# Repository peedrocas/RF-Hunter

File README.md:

# RF-Hunter

Tool that measures the Radio Frequency in a specific location.

My version of the RF-Hunter is a simple, small gadget made from a HMC849A chip and a GRF1201 chip. It also has two antennas, one 2.4GHz and one 5GHz. They switch periodically to measure the amount of radio frequency coming from a specific location.
This way, you can have fun while searching for what device could be emmitting those particular radio waves.

The PCB works on a common ESP32-WROOM-32 DevkitC. You can choose your own screen to use, the 3d printing models and code will need to be adapted! I decided to use a DFR0664 for myself.

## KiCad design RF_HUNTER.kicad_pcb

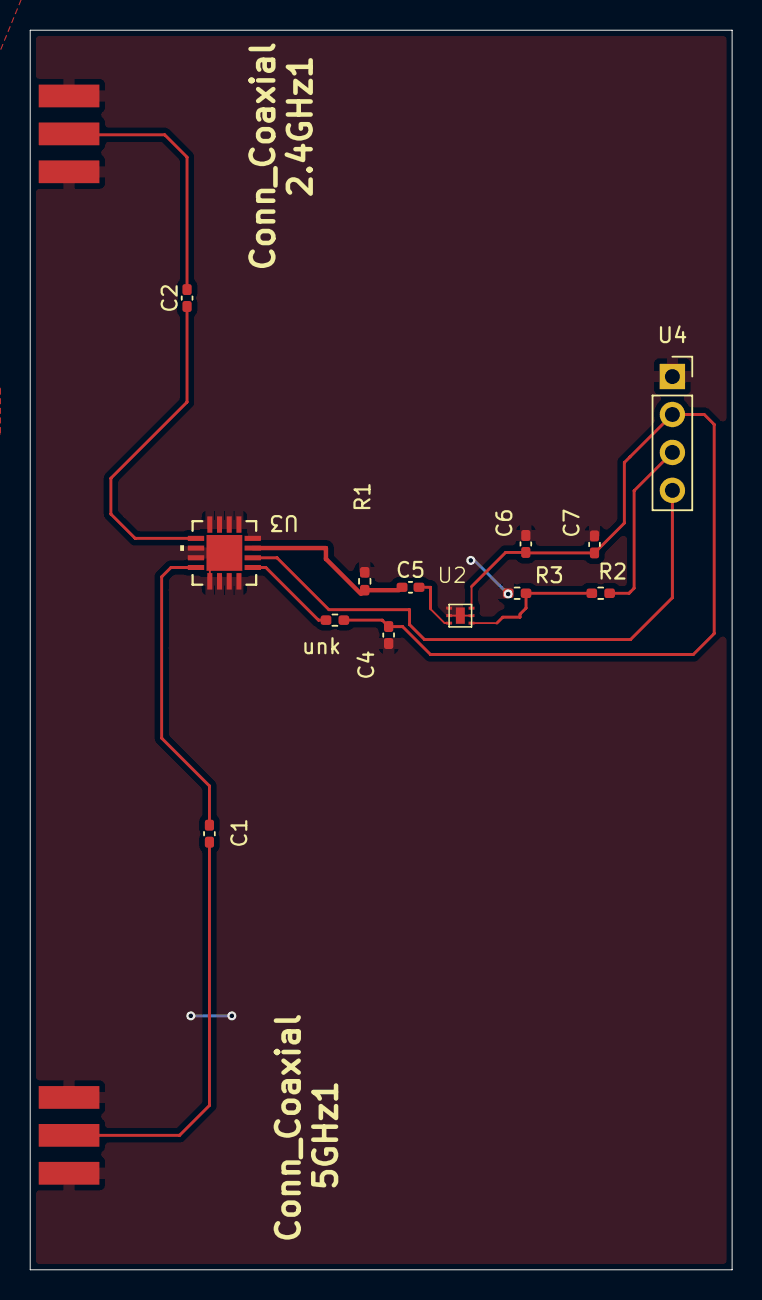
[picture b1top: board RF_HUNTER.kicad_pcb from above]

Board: 4 copper layers, 47.0 x 83.0 mm, 15 parts (0 on the bottom side), 12 nets.

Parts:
2.4GHz1, 5GHz1: Conn_Coaxial; CON-SMA-EDGE
C1, C2, C4, C7: 100pF; C_0402_1005Metric_Pad0.74x0.62mm_HandSolder
C5: 2pF; C_0402_1005Metric_Pad0.74x0.62mm_HandSolder
C6: 100nF; C_0402_1005Metric_Pad0.74x0.62mm_HandSolder
R1: 68Ω; R_0402_1005Metric_Pad0.72x0.64mm_HandSolder
R2: 10kΩ; R_0402_1005Metric_Pad0.72x0.64mm_HandSolder
R3: 20kΩ; R_0402_1005Metric_Pad0.72x0.64mm_HandSolder
U2: GRF1201
U3: HMC849A; CP_16_40_ADI-M
U4: ESP32-DevKitC; PinSocket_1x04_P2.54mm_Vertical
unk: ?; R_0402_1005Metric_Pad0.72x0.64mm_HandSolder

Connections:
GND: 2.4GHz1.2 (Ext), 2.4GHz1.3, 2.4GHz1.4, 2.4GHz1.5, 5GHz1.2 (Ext), 5GHz1.3, 5GHz1.4, 5GHz1.5, C4.1, C6.2, C7.2, R1.1, R3.1, U2.1 (NC/GND), U2.2 (NC/GND), U2.5 (NC/GND), U2.7, U3.4 (GND), U3.5 (EN), U3.6 (GND), U3.7 (GND), U3.8 (GND), U3.10 (GND), U3.11 (GND), U3.13 (GND), U3.14 (GND), U3.15 (GND), U3.16 (GND), U3.17 (GND), U4.1 (3V3)
unnamed: 2.4GHz1.1 (In), C2.2
unnamed: 5GHz1.1 (In), C1.2
unnamed: R2.1, R3.2, U2.4 (DC_Out)
unnamed: C5.2, U2.3 (RF_In)
unnamed: C4.2, C6.1, C7.1, U2.6 (VCC), U4.2 (CHIP_PU), unk.1
unnamed: C2.1, U3.9 (RF1)
unnamed: C1.1, U3.12 (RF2)
unnamed: C5.1, R1.2, U3.3 (RFC)
unnamed: U3.2 (VCTL), U4.4 (SENSOR_VN/GPIO39/ADC1_CH3)
unnamed: U3.1 (VDD), unk.2
unnamed: R2.2, U4.3 (SENSOR_VP/GPIO36/ADC1_CH0)
